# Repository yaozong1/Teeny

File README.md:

Init

Pull the repo
git submodule update --init --recursive

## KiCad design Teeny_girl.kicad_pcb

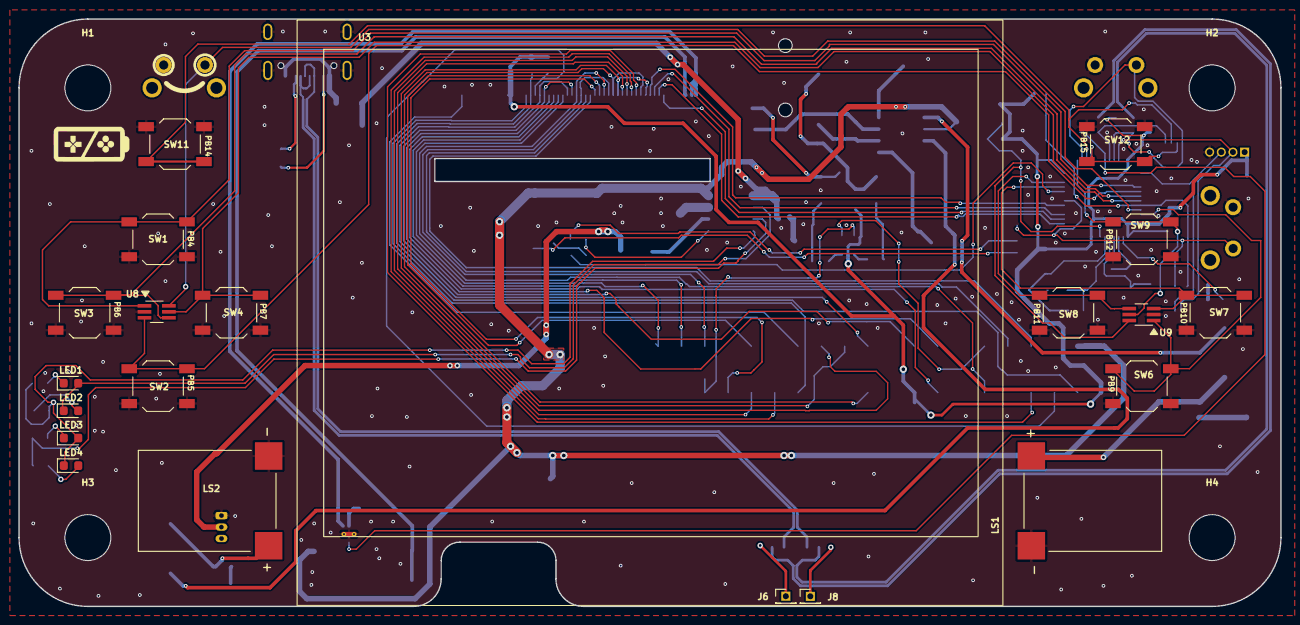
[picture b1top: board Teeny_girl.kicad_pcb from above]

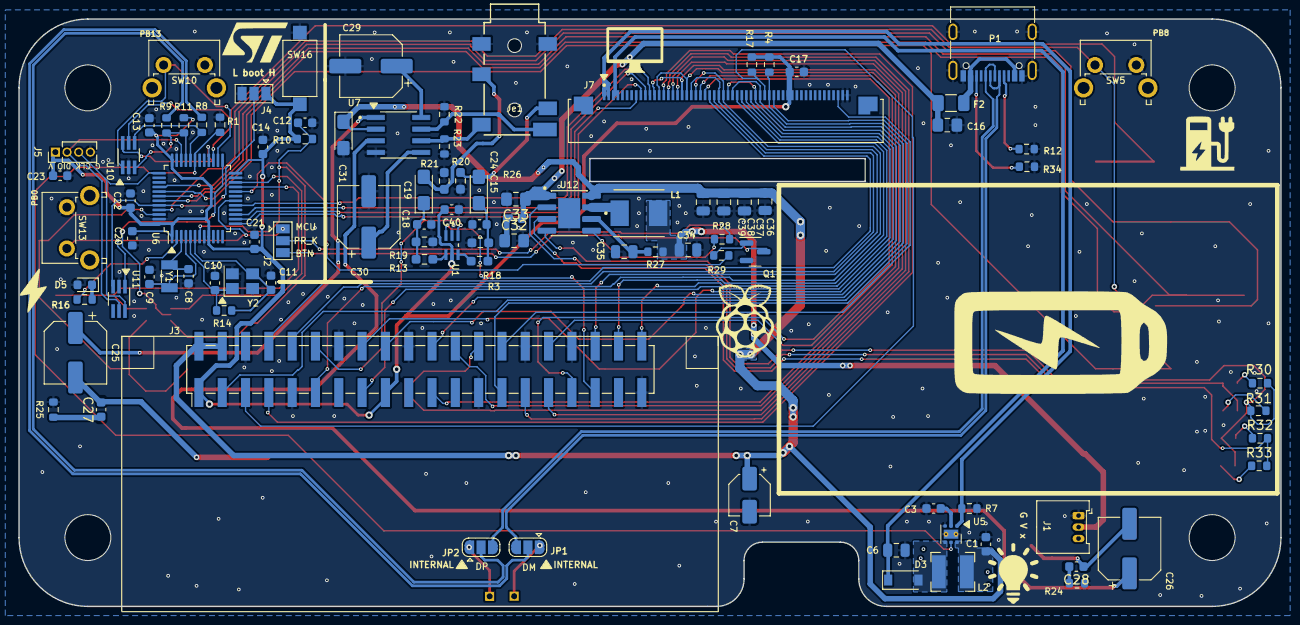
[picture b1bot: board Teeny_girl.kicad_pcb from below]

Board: 2 copper layers, 137.5 x 64.0 mm, 121 parts (96 on the bottom side), 103 nets.

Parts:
C1, C12, C17: 1uF; C_0603_1608Metric
C3: 220nF; C_0603_1608Metric
C6: 1uF; C_0805_2012Metric
C7: 10u; CP_Elec_4x5.4
C8, C9, C10, C11: 20p; C_0603_1608Metric
C13, C14, C15, C18, C20, C21, C22, C23, C27, C28, C40: 100nF; C_0603_1608Metric
C16, C32, C33: 10uF; C_0805_2012Metric_Pad1.18x1.45mm_HandSolder
C19, C24, C31: 47UF; CP_EIA-3216-18_Kemet-A_Pad1.58x1.35mm_HandSolder
C25, C26: 470uF; CP_Elec_6.3x7.7
C29, C30: 100UF; CP_Elec_6.3x5.4
C34, C35, C36, C37, C38, C39: 22uF; C_0805_2012Metric
D3: 500mA; D_SOD-123
D5: LED; LED_0603_1608Metric
F2: 3A; Fuse_1206_3216Metric
H1, H2, H3, H4: MountingHole; MountingHole_5mm
J1: 53048-0310; Molex_PicoBlade_53048-0310_1x03_P1.25mm_Horizontal
J2, J4: Conn_01x03; SolderJumper-3_P1.3mm_Open_Pad1.0x1.5mm
J3: 40HAT; PinHeader_2x20_P2.54mm_Vertical_SMD
J5: Conn_01x04; PinHeader_1x04_P1.27mm_Vertical
J6: DM-; PinHeader_1x01_P1.27mm_Vertical
J7: 54FPC; AMPHENOL_54fpc
J8: DP-; PinHeader_1x01_P1.27mm_Vertical
JP1, JP2: SolderJumper_3_Open; SolderJumper-3_P1.3mm_Open_RoundedPad1.0x1.5mm
Je1: PJ-342B-TX-SMT; PJ-342B-TX-SMT_XKB
L1: 1uH; IND_MGV05021R0M-10
L2: 22uH; L_Bourns-SRN4018
LED1, LED2, LED3, LED4: LED; LED_0603_1608Metric
LS1, LS2: KAAG20008C-10A; CUI_CMS-15116-SP
P1: USB_C_USB2.0; USB_C_Receptacle_G-Switch_GT-USB-7010ASV
Q1: BC846; SOT-23
R1, R4, R10, R17, R22, R23, R28: 10K; R_0603_1608Metric
R3, R13: 220; R_0603_1608Metric_Pad0.98x0.95mm_HandSolder
R7: 10; R_0603_1608Metric
R8, R9: 20; R_0603_1608Metric
R11: 1k5; R_0603_1608Metric
R12, R34: 5K1; R_0603_1608Metric
R14: 1M; R_0603_1608Metric
R16: 510; R_0603_1608Metric
R18, R19: 100; R_0603_1608Metric_Pad0.98x0.95mm_HandSolder
R20, R21: 1K8; R_0603_1608Metric_Pad0.98x0.95mm_HandSolder
R24, R25: 4.7; R_0603_1608Metric
R26: 2; R_0603_1608Metric
R27: 0.5; R_0603_1608Metric
R29: 100K; R_0603_1608Metric
R30, R31, R32, R33: 1k; R_0603_1608Metric
SW1, SW2, SW3, SW4, SW6, SW7, SW8, SW9, SW11, SW12: SW_Push; SW_SPST_TL3342
SW5: locked; SW_Tactile_SPST_Angled_PTS645Vx39-2LFS
SW10, SW13: SW_Push; SW_Tactile_SPST_Angled_PTS645Vx39-2LFS
SW16: SW_Push_Open; SW_SPST_CK_RS282G05A3
U1: NC7WZ16P6X; SOT65P210X110-6N
U3: Display-position; Display-position_3.5
U5: TPS61161_; WSON-6-1EP_2x2mm_P0.65mm_EP1x1.6mm_ThermalVias
U6: STM32F103C6T6; LQFP-48_7x7mm_P0.5mm
U7: TDA2822D; SOIC127P600X175-8N
U8, U9, U10, U11: PESD5V0L5UV; SOT-363_SC-70-6_Handsoldering
U12: IP5306; IP5306 SOIC9P127_490X600X170L84X42T330X241N
Y1: 32.768k; Crystal_SMD_3215-2Pin_3.2x1.5mm
Y2: 8M; Crystal_SMD_Abracon_ABM8AIG-4Pin_3.2x2.5mm

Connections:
5V0_SW: C1.1, C7.1, C31.1, C36.1, C37.1, C38.1, C39.1, J3.2 (P5V), J3.4 (P5V), L2.1, U5.6 (VIN), U7.2, U12.8 (VOUT)
5V_USB: C16.1, C33.1, F2.2, R26.2, U12.1 (VCC)
/3V3: C13.1, C14.1, C17.2, C20.1, C21.1, C22.1, C23.1, C40.1, J3.1 (P3V3), J3.17 (P3V3), J4.1, J5.1, J7.41 (IOVCC), J7.42 (VCI), R4.1, R10.1, R11.2, R17.1, SW16.2 (B), U1.5 (VCC), U6.1 (VBAT), U6.9 (VDDA), U6.24 (VDD), U6.36 (VDD), U6.48 (VDD)
/3V7: C34.1, J1.2, L1.2, R27.2
/AUDIO_L: Je1.4, R22.1, U7.7
/AUDIO_R: Je1.7, R23.1, U7.6
/B2: J3.7 (BCM4), J7.14 (B2)
/B3: J3.29 (BCM5), J7.15 (B3)
/B4: J3.31 (BCM6), J7.16 (B4)
/B5: J3.26 (BCM7), J7.17 (B5)
/B6: J3.24 (BCM8), J7.12 (B0), J7.18 (B6)
/B7: J3.21 (BCM9), J7.13 (B1), J7.19 (B7)
/BOOT0: J4.2, U6.44 (BOOT0), U11.3 (A3)
/Backlight_CTRL: R1.1, U5.5 (CTRL), U6.31 (PA10)
/DE: J3.28 (BCM1), J7.52 (DE)
/G2: J3.32 (BCM12), J7.22 (G2)
/G3: J3.33 (BCM13), J7.23 (G3)
/G4: J3.8 (BCM14), J7.24 (G4)
/G5: J3.10 (BCM15), J7.25 (G5)
/G6: J3.36 (BCM16), J7.20 (G0), J7.26 (G6)
/G7: J3.11 (BCM17), J7.21 (G1), J7.27 (G7)
/HSYNC: J3.5 (BCM3), J7.36 (HSYNC), R17.2
/KEY_A: SW6.1, U6.46 (PB9), U9.1 (A1)
/KEY_B: SW7.1, U6.21 (PB10), U9.3 (A3)
/KEY_C: SW8.1, U6.22 (PB11), U9.4 (A4)
/KEY_D: SW9.1, U6.25 (PB12), U9.5 (A5)
/KEY_DOWN: SW2.1, U6.41 (PB5), U8.3 (A3)
/KEY_LEFT: SW3.1, U6.42 (PB6), U8.4 (A4)
/KEY_RIGHT: SW4.1, U6.43 (PB7), U8.5 (A5)
/KEY_UP: SW1.1, U6.40 (PB4), U8.1 (A1)
/LED_A: C6.1, D3.1 (K), J7.3 (LEDA), J7.4 (LEDA)
/LED_K: J7.1 (LEDK), J7.2 (LEDK), R7.1, U5.1 (FB)
/LEFT_TRIGGER: SW5.1, U6.45 (PB8), U8.6 (A6)
/ON_OFF: J2.1, SW13.1, U6.18 (PB0), U11.1 (A1)
/PA11: R8.2, U6.32 (PA11), U10.4 (A4)
/PA12: R9.2, R11.1, U6.33 (PA12), U10.3 (A3)
/PC13: R16.2, U6.2 (PC13-TAMPER_RTC)
/PC14: C8.2, U6.3 (PC14_OSC32_IN), Y1.1
/PC15: C9.2, U6.4 (PC15_OSC32_OUT), Y1.2
/PCLK: J3.27 (BCM0), J7.38 (DCLK)
/PD0: C10.2, R14.2, U6.5 (PD0_OSC_IN), Y2.1
/PD1: C11.2, R14.1, U6.6 (PD1_OSC_OUT), Y2.3
/PWM_0: J3.12 (BCM18), U1.1 (A1)
/PWM_1: J3.35 (BCM19), U1.3 (A2)
/PWR_EN: R29.2, U6.20 (PB2)
/R2: J3.38 (BCM20), J7.30 (R2)
/R3: J3.40 (BCM21), J7.31 (R3)
/R4: J3.15 (BCM22), J7.32 (R4)
/R5: J3.16 (BCM23), J7.33 (R5)
/R6: J3.18 (BCM24), J7.28 (R0), J7.34 (R6)
/R7: J3.22 (BCM25), J7.29 (R1), J7.35 (R7)
/RIGHT_TRIGGER: SW10.1, U6.26 (PB13), U10.1 (A1)
/SELECT: SW12.1, U6.28 (PB15), U10.6 (A6)
/SPI_CLK: J7.10 (SPCLK), U6.15 (PA5)
/SPI_CS: J7.9 (SPRNA), U6.13 (PA3)
/SPI_DATA: J7.11 (SPDAT), U6.17 (PA7)
/SPI_RESET: J7.8 (REST), U6.14 (PA4)
/START: SW11.1, U6.27 (PB14), U10.5 (A5)
/STM32_RESET: C12.1, R10.2, U6.7 (NRST), U9.6 (A6)
/SWCLK: J5.3, U6.37 (PA14), U11.6 (A6)
/SWDIO: J5.2, U6.34 (PA13), U11.5 (A5)
/USB+: JP2.2 (C), R9.1
/USB-: JP1.2 (C), R8.1
/USB_N: JP1.3 (B), P1.A7 (D-), P1.B7 (D-)
/USB_P: JP2.3 (B), P1.A6 (D+), P1.B6 (D+)
/VSYNC: J3.3 (BCM2), J7.37 (VSYNC), R4.2
GND: C1.2, C3.2, C6.2, C7.2, C8.1, C9.1, C10.1, C11.1, C12.2, C13.2, C14.2, C15.1, C16.2, C17.1, C18.2, C20.2, C21.2, C22.2, C23.2, C29.2, C30.2, C31.2, C32.2, C33.2, C34.2, C35.2, C36.2, C37.2, C38.2, C39.2, C40.2, D5.2 (A), J1.1, J3.6 (GND), J3.9 (GND), J3.14 (GND), J3.20 (GND), J3.25 (GND), J3.30 (GND), J3.34 (GND), J3.39 (GND), J4.3, J5.4, J7.53 (GND), J7.54 (GND), Je1.2, Je1.5, LS1.N, LS2.N, P1.A1 (GND), P1.A12 (GND), P1.B1 (GND), P1.B12 (GND), P1.S1 (SHIELD), Q1.2 (E), R1.2, R7.2, R12.2, R18.2, R19.1, R20.2, R21.1, R22.2, R23.2, R24.2, R25.1, R34.2, SW1.2, SW2.2, SW3.2, SW4.2, SW5.2, SW6.2, SW7.2, SW8.2, SW9.2, SW10.2, SW11.2, SW12.2, SW13.2, SW16.1 (A), U1.2 (GND), U5.3 (GND), U5.7 (PAD), U6.8 (VSSA), U6.23 (VSS), U6.35 (VSS), U6.47 (VSS), U7.4, U8.2 (A2), U9.2 (A2), U10.2 (A2), U11.2 (A2), U12.9 (GND), Y2.2, Y2.4
unnamed: C15.2, C24.1, R3.2, R18.1
unnamed: C18.1, C19.1, R13.2, R19.2
unnamed: C19.2, Je1.6, R21.2
unnamed: C24.2, Je1.3, R20.1
unnamed: C25.1, U7.1
unnamed: C25.2, C27.2, LS1.P
unnamed: C26.1, U7.3
unnamed: C26.2, C28.1, LS2.P
unnamed: C27.1, R25.2
unnamed: C28.2, R24.1
unnamed: C29.1, U7.8
unnamed: C30.1, U7.5
unnamed: C32.1, R26.1
unnamed: D3.2 (A), L2.2, U5.4 (SW)
unnamed: D5.1 (K), R16.1
unnamed: F2.1, P1.A4 (VBUS), P1.A9 (VBUS), P1.B4 (VBUS), P1.B9 (VBUS)
unnamed: J2.2, R28.1
unnamed: J2.3, Q1.3 (C)
unnamed: J6.1, JP1.1 (A)
unnamed: J8.1, JP2.1 (A)
unnamed: LED1.2 (A), LED2.1 (K), U12.2 (LED1)
unnamed: LED1.1 (K), R30.1
unnamed: LED2.2 (A), R31.1
unnamed: LED3.2 (A), LED4.1 (K), R30.2, R31.2, U12.4 (LED3)
unnamed: LED3.1 (K), R32.1
unnamed: LED4.2 (A), R33.1
unnamed: P1.A5 (CC1), R12.1
unnamed: P1.B5 (CC2), R34.1
unnamed: Q1.1 (B), R29.1
unnamed: R3.1, U1.6 (Y1)
unnamed: R13.1, U1.4 (Y2)
unnamed: C3.1, U5.2 (COMP)
unnamed: C35.1, R27.1, U12.6 (BAT)
unnamed: R28.2, U12.5 (KEY)
unnamed: R32.2, R33.2, U12.3 (LED2)
unnamed: L1.1, U12.7 (SW)

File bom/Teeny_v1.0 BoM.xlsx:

| References | Value | Footprint | Description | MPN | Quantity
1 | C13, C14, C15, C18, C20, C21, C22, C23, C27, C28, C40 | 100nF | C_0603_1608Metric |  | C30926 | 11
2 | C34, C35, C36, C37, C38, C39 | 22uF | C_0805_2012Metric |  | C45783 | 6
3 | C8, C9, C10, C11 | 20p | C_0603_1608Metric |  | C91702 | 4
4 | C1, C12, C17 | 1uF | C_0603_1608Metric |  | C15849 | 3
5 | C16, C32, C33 | 10uF | C_0805_2012Metric_Pad1.18x1.45mm_HandSolder |  | C15850 | 3
6 | C19, C24, C31 | 47UF | CP_EIA-3216-18_Kemet-A_Pad1.58x1.35mm_HandSolder |  | C129570 | 3
7 | C25, C26 | 470uF | CP_Elec_6.3x7.7 |  | C2977552 | 2
8 | C29, C30 | 100UF | CP_Elec_6.3x5.4 |  | C37308 | 2
9 | C3 | 220nF | C_0603_1608Metric |  | C21120 | 1
10 | C6 | 1uF | C_0805_2012Metric |  | C28323 | 1
11 | C7 | 10u | CP_Elec_4x5.4 |  | C72485 | 1
12 | R1, R4, R10, R17, R22, R23, R28 | 10K | R_0603_1608Metric |  | C25804 | 7
13 | R30, R31, R32, R33 | 1k | R_0603_1608Metric |  | C22548 | 4
14 | R3, R13 | 220 | R_0603_1608Metric_Pad0.98x0.95mm_HandSolder |  | C22962 | 2
15 | R8, R9 | 20 | R_0603_1608Metric |  | C22859 | 2
16 | R12, R34 | 5K1 | R_0603_1608Metric |  | C23186 | 2
17 | R18, R19 | 100 | R_0603_1608Metric_Pad0.98x0.95mm_HandSolder |  | C105588 | 2
18 | R20, R21 | 1K8 | R_0603_1608Metric_Pad0.98x0.95mm_HandSolder |  | C4177 | 2
19 | R24, R25 | 4.7 | R_0603_1608Metric |  | C23164 | 2
20 | R7 | 10 | R_0603_1608Metric |  | C22859 | 1
21 | R11 | 1k5 | R_0603_1608Metric |  | C22843 | 1
22 | R14 | 1M | R_0603_1608Metric |  | C136593 | 1
23 | R16 | 510 | R_0603_1608Metric |  | C23193 | 1
24 | R26 | 2 | R_0603_1608Metric |  | C22977 | 1
25 | R27 | 0.5 | R_0603_1608Metric |  | C45312 | 1
26 | R29 | 100K | R_0603_1608Metric |  | C14675 | 1
27 | L1 | 1uH | IND_MGV05021R0M-10 | TMPC0502HP-1R0MG-D | C305205 | 1
28 | L2 | 22uH | L_Bourns-SRN4018 | SRN4018TA-220M / VLCF5020T-220MR75-1 | C87576 | 1
29 | D5, LED1, LED2, LED3, LED4 | LED | LED_0603_1608Metric |  | C84266 | 5
30 | D3 | 500mA | D_SOD-123 | MBR0540T1G | C21353 | 1
31 | U8, U9, U10, U11 | PESD5V0L5UV | SOT-363_SC-70-6_Handsoldering |  | C3021130 | 4
32 | U1 | NC7WZ16P6X | SOT65P210X110-6N | NC7WZ16P6X | C114148 | 1
33 | U3 | Display-position | Display-position_3.5 |  | DNP | 1
34 | U5 | TPS61161_ | WSON-6-1EP_2x2mm_P0.65mm_EP1x1.6mm_ThermalVias | TPS61161DRVR | C324075 | 1
35 | U6 | STM32F103C6T6 | LQFP-48_7x7mm_P0.5mm |  | TB | 1
36 | U7 | TDA2822D | SOIC127P600X175-8N | Amplifier IC 1-Channel (Mono) or 2-Channel (Stereo) Class AB 8-SOIC | C5145398 | 1
37 | U12 | IP5306 | IP5306 SOIC9P127_490X600X170L84X42T330X241N | Fully-Integrated Power Bank System-On-Chip with 2.1A charger, 2.4A discharger | C181692 | 1
38 | Y1 | 32.768k | Crystal_SMD_3215-2Pin_3.2x1.5mm |  | C620155 | 1
39 | Y2 | 8M | Crystal_SMD_Abracon_ABM8AIG-4Pin_3.2x2.5mm |  | C5181477 | 1
40 | F2 | 3A | Fuse_1206_3216Metric | 0685T3000-01 | C206970 | 1
41 | SW1, SW2, SW3, SW4, SW6, SW7, SW8, SW9, SW11, SW12 | SW_Push | SW_SPST_TL3342 | TS-1087S-01626 | C455263 | 10
42 | SW5, SW10, SW13 | SW_Push | SW_Tactile_SPST_Angled_PTS645Vx39-2LFS | TS-1002N-BR04516 | C720330 | 3
43 | SW16 | SW_Push_Open | SW_SPST_CK_RS282G05A3 | TS-1092S-B3D2-G | C520860 | 1
44 | JP1, JP2 | SolderJumper_3_Open | SolderJumper-3_P1.3mm_Open_RoundedPad1.0x1.5mm |  | DNP | 2
45 | LS1, LS2 | KAAG20008C-10A | CUI_CMS-15116-SP | Speaker 1W, 8Ω ,88 dB (SPL), 850Hz, SMD type | TB | 2
46 | Je1 | PJ-342B-TX-SMT | PJ-342B-TX-SMT_XKB |  | C388632 | 1
47 | Q1 | BC846 | SOT-23 |  | C87062 | 1
48 | J2, J4 | Conn_01x03 | SolderJumper-3_P1.3mm_Open_Pad1.0x1.5mm |  | DNP | 2
49 | J1 | 53048-0310 | Molex_PicoBlade_53048-0310_1x03_P1.25mm_Horizontal | CONN HEADER R/A 3POS 1.25MM | C505275 | 1
50 | J3 | 40HAT | PinHeader_2x20_P2.54mm_Vertical_SMD |  | DNP | 1
51 | J5 | Conn_01x04 | PinHeader_1x04_P1.27mm_Vertical |  | DNP | 1
52 | J6 | DM- | PinHeader_1x01_P1.27mm_Vertical |  | DNP | 1
53 | J7 | 54FPC | AMPHENOL_54fpc | 54 Position FFC, FPC Connector Contacts, Top 0.020 (0.50mm) Surface Mount, Righ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 | C262285 | 1
54 | J8 | DP- | PinHeader_1x01_P1.27mm_Vertical |  | DNP | 1
55 | P1 | USB_C_USB2.0 | USB_C_Receptacle_G-Switch_GT-USB-7010ASV |  | C223907 | 1

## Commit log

2024-01-17 the first commit
2024-01-17 saved
2024-02-20 save 2/20
2024-02-21 updated and delete old battery charger mcp73871
2024-02-23 done but RGB666 should be changed to mode6
2024-02-27 keep track of latest lib
2024-02-29 update usbc info
